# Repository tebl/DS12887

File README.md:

# Simple DS12887
I'm not going to add a complete set of documentation for this, mostly as the chips will disappear before long. And honestly - the project is more of a reminder as to what goes where instead of something that you'd need a complete PCB for. It's great if you need it, or prefer the look of one as compared to some components soldered directly to the pins. I can't tell you which computers it would be compatible with as there are so many computers and so little time, but if you found a *Dallas DS12887* soldered to your "vintage IBM PC or compatible" mainboard - then this is an option as long as supplies last.

As for components you're going to need a *Dallas DS12885*, a 32.768Khz crystal (3x8mm, 6pf if you're lucky enough to find one with a datasheet) as well as a CR2032 battery holder. Assembly is easy - all you need is to put the PCB on top of your chip, then bend up and over any pins that have a corresponding solder pad on the top. Solder it in place, add crystal and wire the battery holder leads in the indicated places. The reason for the external battery holder is that on many of my motherboards, a board with a battery directly on it would mean that I couldn't use some of the slots - and I'm still not quite ready to give up on my ISA soundcards.

- Shared project on [PCBWay](https://www.pcbway.com/project/shareproject/Simple_DS12887_dbfa00e8.html)

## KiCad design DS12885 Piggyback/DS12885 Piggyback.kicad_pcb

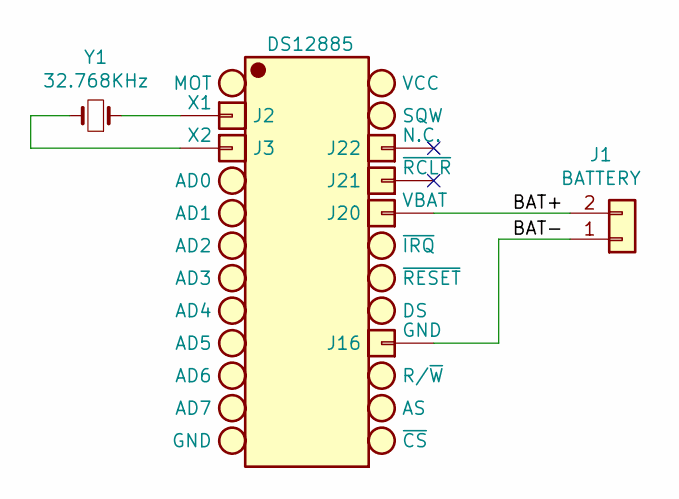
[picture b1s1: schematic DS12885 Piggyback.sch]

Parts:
J1: BATTERY; edge_pins_1x02
J2: X1; edge_pins_1x01
J3: X2; edge_pins_1x01
J16: GND; edge_pins_1x01
J20: VBAT; edge_pins_1x01
J21: ~RCLR; edge_pins_1x01
J22: N.C.; edge_pins_1x01
Y1: 32.768KHz; edge_pins_1x02

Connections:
/BAT+: J1.2, J20.1
/BAT-: J1.1, J16.1
unnamed: J2.1, Y1.1
unnamed: J3.1, Y1.2

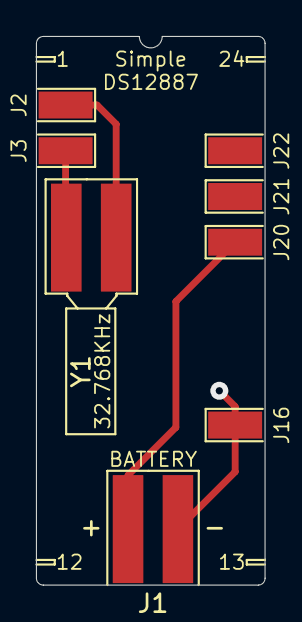
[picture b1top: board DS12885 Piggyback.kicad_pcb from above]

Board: 2 copper layers, 12.7 x 30.5 mm, 8 parts (0 on the bottom side), 4 nets.

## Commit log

2022-11-01 Initial version
2024-06-14 Add images
2024-06-14 Add schematic
2024-06-14 Add datasheet

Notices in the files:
DS12885 Piggyback/DS12885 Piggyback.kicad_pcb:
Licensed under CERN OHL v1.2
